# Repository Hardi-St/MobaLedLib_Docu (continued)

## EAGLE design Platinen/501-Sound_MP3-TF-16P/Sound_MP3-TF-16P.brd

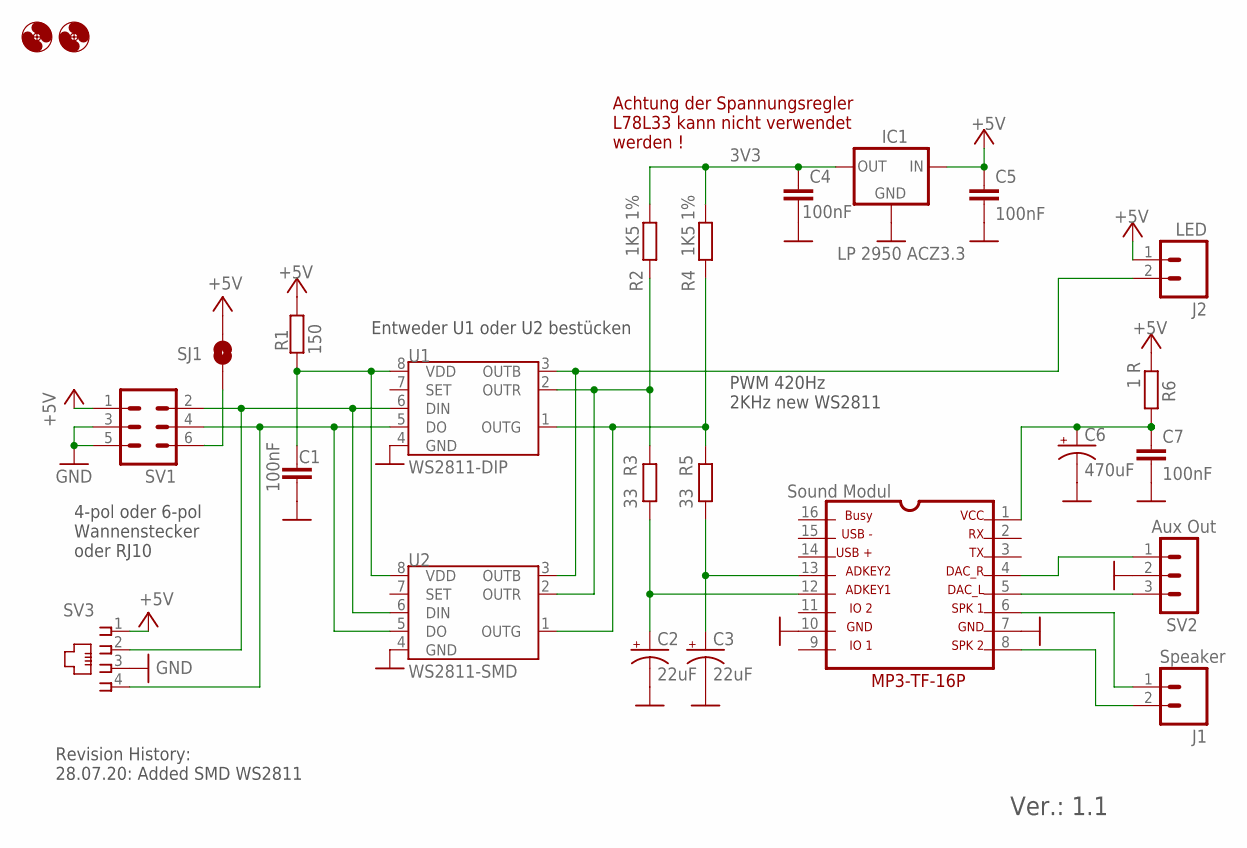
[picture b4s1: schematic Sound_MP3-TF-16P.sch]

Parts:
C1, C4, C5, C7: 100nF; CAP-PTH-SMALL-KIT
C2, C3: 22uF; CAPACITOR_CPOL-RADIAL-22UF
C6: 470uF; SPARKFUN-CAPACITORS_CPOL-RADIAL-100UF-25V
H1, H3: MOUNT-HOLE3.0; 3,0
IC1: LP 2950 ACZ3.3; 78LXX
J1: Speaker; 1X02
J2: LED; 1X02
MOD1: Sound Modul; MP3-TF-16P_MP3-TF-16P
R1: 150; RCL_0204/5
R2, R4: 1K5 1%; RCL_0204/5
R3, R5: 33; RCL_0204/5
R6: 1 R; RCL_0204/5
SJ1: Pin6 = 5V; SJ_2S-NO
SV1: ML6
SV2: Aux Out; MA03-1
SV3: RJ10RJ10_WO_OVERLAP; RJ10_NO_OVERLAP_BORDER
U1: WS2811-DIP; S3PO_MODUL_WS2811_SOUND_MP3-TF-16P_WS2811_AND_ATTINY_WS2811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
U2: WS2811-SMD; S3PO_MODUL_WS2811_SOUND_MP3-TF-16P_WS2811_AND_ATTINY_WS2811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

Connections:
3V3: C4.1, IC1.OUT, R2.1, R4.1
+5V: C5.1, IC1.IN, J2.1, R1.2, R6.1, SJ1.1, SV1.1, SV3.1
+5V1: SJ1.2, SV1.6
G1: R4.2, R5.1, U1.1 (OUTG), U2.1 (OUTG)
GND: C1.2, C2.2 (-), C3.2 (-), C4.2, C5.2, C6.2 (-), C7.2, IC1.GND, MOD1.7, MOD1.10, SV1.3, SV1.5, SV2.2, SV3.3, U1.4 (GND), U2.4 (GND)
unnamed: MOD1.5, SV2.3
unnamed: MOD1.4, SV2.1
unnamed: SV1.2, SV3.2, U1.6 (DIN), U2.6 (DIN)
unnamed: SV1.4, SV3.4, U1.5 (DO), U2.5 (DO)
unnamed: J1.1, MOD1.6
unnamed: J1.2, MOD1.8
unnamed: C2.1 (+), MOD1.12, R3.2
unnamed: C3.1 (+), MOD1.13, R5.2
unnamed: C6.1 (+), C7.1, MOD1.1, R6.2
unnamed: J2.2, U1.3 (OUTB), U2.3 (OUTB)
PWR1: C1.1, R1.1, U1.8 (VDD), U2.8 (VDD)
R1: R2.2, R3.1, U1.2 (OUTR), U2.2 (OUTR)

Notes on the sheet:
PWM 420Hz 2KHz new WS2811
4-pol oder 6-pol Wannenstecker oder RJ10
Achtung der Spannungsregler L78L33 kann nicht verwendet werden !
Revision History: 28.07.20: Added SMD WS2811
Ver.: 1.1
Entweder U1 oder U2 bestücken

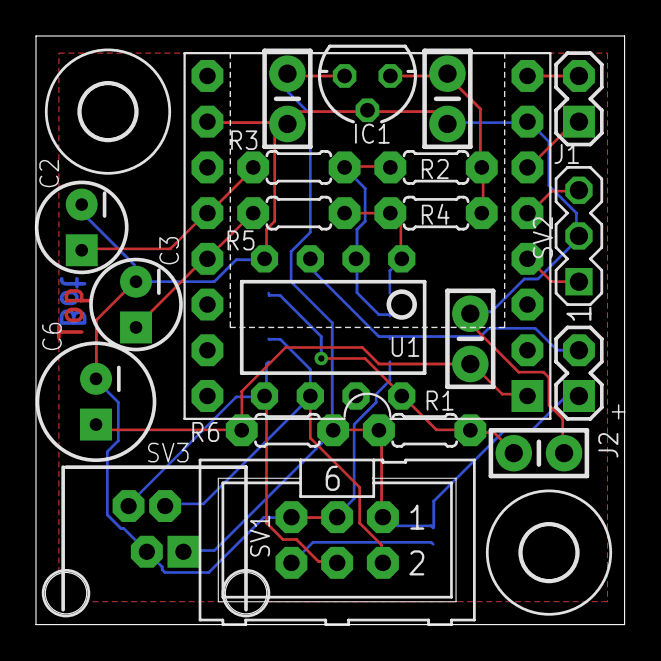
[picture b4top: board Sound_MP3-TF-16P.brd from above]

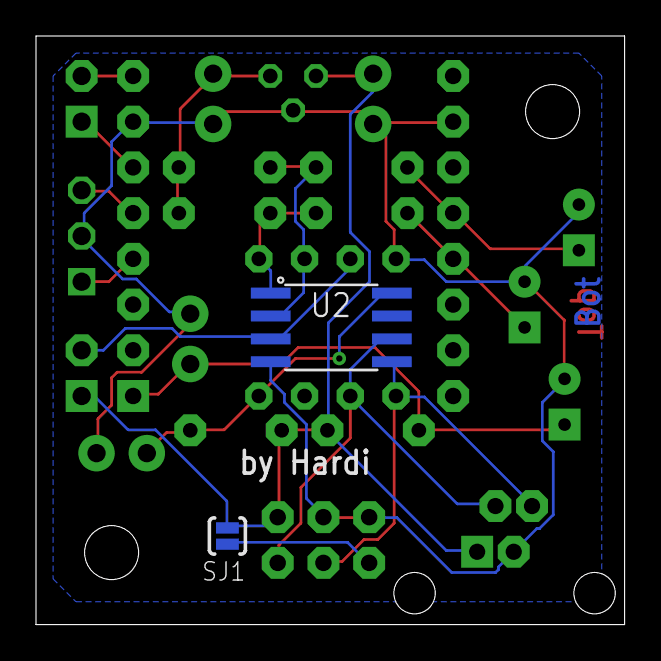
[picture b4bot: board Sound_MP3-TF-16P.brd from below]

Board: 2 copper layers, 32.7 x 32.7 mm, 25 parts (2 on the bottom side), 17 nets.

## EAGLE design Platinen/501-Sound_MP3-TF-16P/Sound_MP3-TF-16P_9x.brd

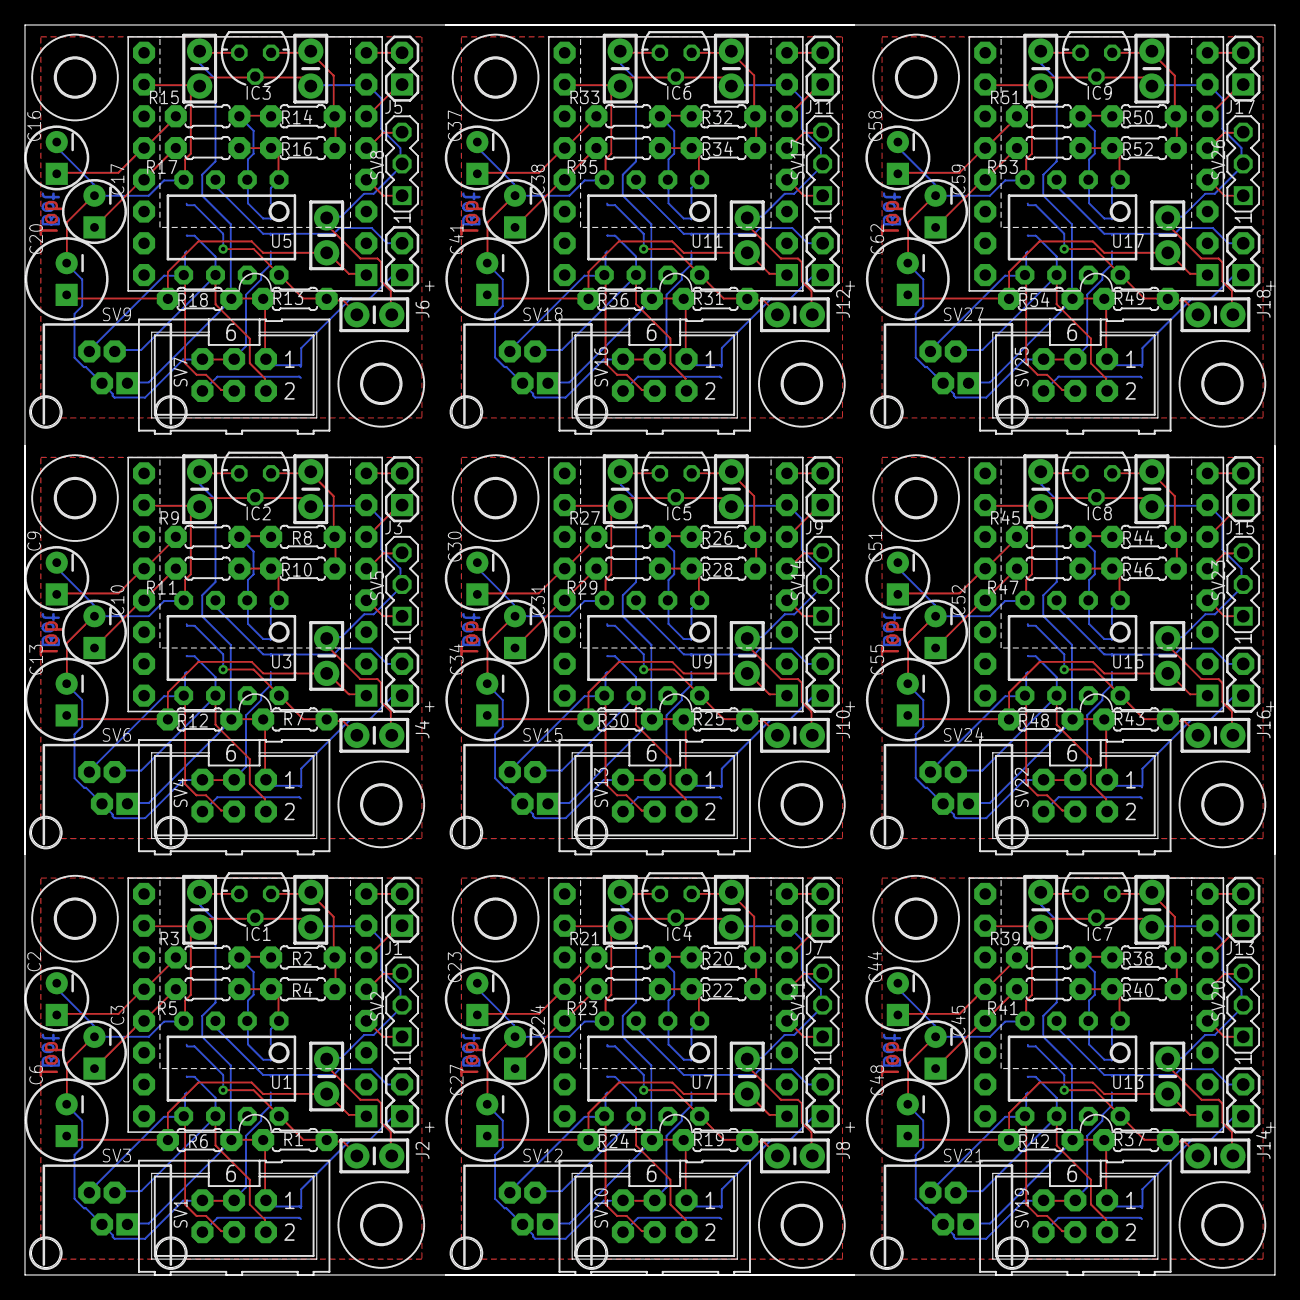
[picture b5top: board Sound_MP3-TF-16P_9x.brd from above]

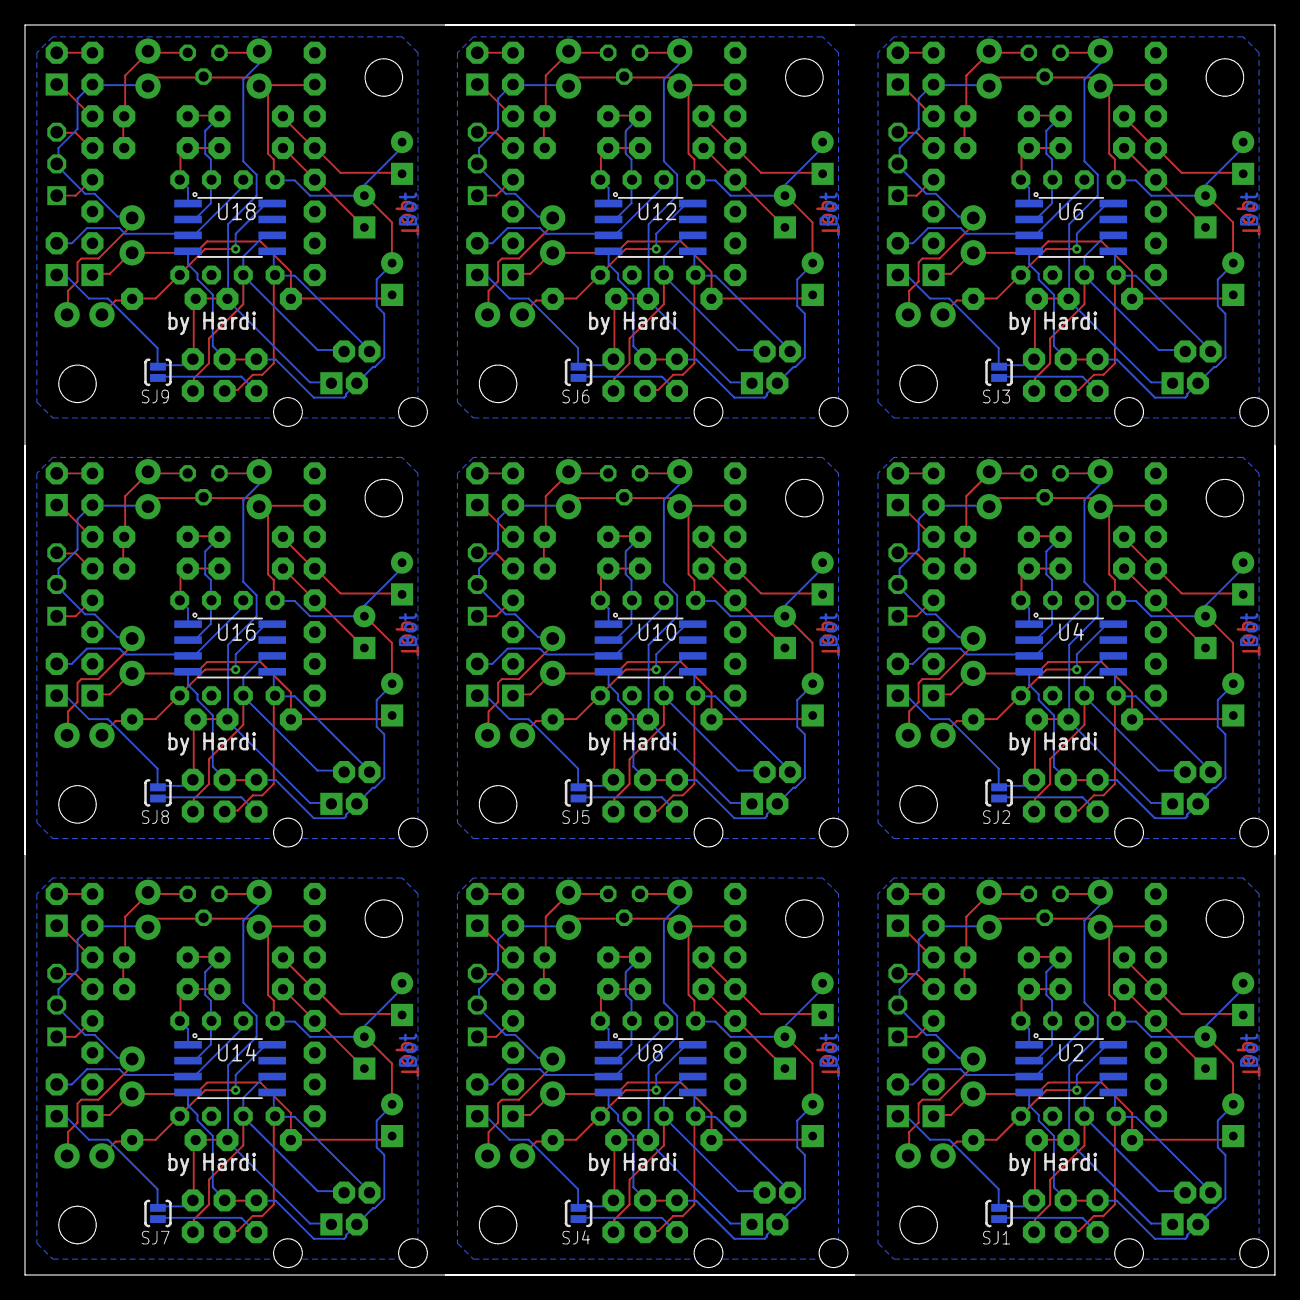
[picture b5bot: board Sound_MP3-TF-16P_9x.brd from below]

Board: 2 copper layers, 100.0 x 100.0 mm, 225 parts (18 on the bottom side), 153 nets.

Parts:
C1, C4, C5, C7, C8, C11, C12, C14, C15, C18, C19, C21, C22, C25, C26, C28, C29, C32, C33, C35, C36, C39, C40, C42, C43, C46, C47, C49, C50, C53, C54, C56, C57, C60, C61, C63: 100nF; CAP-PTH-SMALL-KIT
C2, C3, C9, C10, C16, C17, C23, C24, C30, C31, C37, C38, C44, C45, C51, C52, C58, C59: 22uF; CAPACITOR_CPOL-RADIAL-22UF
C6, C13, C20, C27, C34, C41, C48, C55, C62: 470uF; SPARKFUN-CAPACITORS_CPOL-RADIAL-100UF-25V
H1, H2, H3, H4, H5, H6, H7, H8, H9, H10, H11, H12, H13, H14, H15, H16, H17, H18: MOUNT-HOLE3.0; 3,0
IC1, IC2, IC3, IC4, IC5, IC6, IC7, IC8, IC9: LP 2950 ACZ3.3; 78LXX
J1, J3, J5, J7, J9, J11, J13, J15, J17: Speaker; 1X02
J2, J4, J6, J8, J10, J12, J14, J16, J18: LED; 1X02
MOD1, MOD2, MOD3, MOD4, MOD5, MOD6, MOD7, MOD8, MOD9: Sound Modul; MP3-TF-16P_MP3-TF-16P
R1, R7, R13, R19, R25, R31, R37, R43, R49: 150; RCL_0204/5
R2, R4, R8, R10, R14, R16, R20, R22, R26, R28, R32, R34, R38, R40, R44, R46, R50, R52: 1K5 1%; RCL_0204/5
R3, R5, R9, R11, R15, R17, R21, R23, R27, R29, R33, R35, R39, R41, R45, R47, R51, R53: 33; RCL_0204/5
R6, R12, R18, R24, R30, R36, R42, R48, R54: 1 R; RCL_0204/5
SJ1, SJ2, SJ3, SJ4, SJ5, SJ6, SJ7, SJ8, SJ9: Pin6 = 5V; SJ_2S-NO
SV1, SV4, SV7, SV10, SV13, SV16, SV19, SV22, SV25: ML6
SV2, SV5, SV8, SV11, SV14, SV17, SV20, SV23, SV26: Aux Out; MA03-1
SV3, SV6, SV9, SV12, SV15, SV18, SV21, SV24, SV27: RJ10RJ10_WO_OVERLAP; RJ10_NO_OVERLAP_BORDER
U1, U3, U5, U7, U9, U11, U13, U15, U17: WS2811-DIP; S3PO_MODUL_WS2811_SOUND_MP3-TF-16P_WS2811_AND_ATTINY_WS2811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
U2, U4, U6, U8, U10, U12, U14, U16, U18: WS2811-SMD; S3PO_MODUL_WS2811_SOUND_MP3-TF-16P_WS2811_AND_ATTINY_WS2811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

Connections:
3V1: C11.1, IC2.OUT, R8.1, R10.1
3V2: C18.1, IC3.OUT, R14.1, R16.1
3V3: C4.1, IC1.OUT, R2.1, R4.1
3V4: C25.1, IC4.OUT, R20.1, R22.1
3V5: C32.1, IC5.OUT, R26.1, R28.1
3V6: C39.1, IC6.OUT, R32.1, R34.1
3V7: C46.1, IC7.OUT, R38.1, R40.1
3V8: C53.1, IC8.OUT, R44.1, R46.1
3V9: C60.1, IC9.OUT, R50.1, R52.1
+5V: C5.1, IC1.IN, J2.1, R1.2, R6.1, SJ1.1, SV1.1, SV3.1
+5V1: SJ1.2, SV1.6
+5V2: C12.1, IC2.IN, J4.1, R7.2, R12.1, SJ2.1, SV4.1, SV6.1
+5V3: SJ2.2, SV4.6
+5V4: C19.1, IC3.IN, J6.1, R13.2, R18.1, SJ3.1, SV7.1, SV9.1
+5V5: SJ3.2, SV7.6
+5V6: C26.1, IC4.IN, J8.1, R19.2, R24.1, SJ4.1, SV10.1, SV12.1
+5V7: SJ4.2, SV10.6
+5V8: C33.1, IC5.IN, J10.1, R25.2, R30.1, SJ5.1, SV13.1, SV15.1
+5V9: SJ5.2, SV13.6
+5V10: C40.1, IC6.IN, J12.1, R31.2, R36.1, SJ6.1, SV16.1, SV18.1
+5V11: SJ6.2, SV16.6
+5V12: C47.1, IC7.IN, J14.1, R37.2, R42.1, SJ7.1, SV19.1, SV21.1
+5V13: SJ7.2, SV19.6
+5V14: C54.1, IC8.IN, J16.1, R43.2, R48.1, SJ8.1, SV22.1, SV24.1
+5V15: SJ8.2, SV22.6
+5V16: C61.1, IC9.IN, J18.1, R49.2, R54.1, SJ9.1, SV25.1, SV27.1
+5V17: SJ9.2, SV25.6
G1: R4.2, R5.1, U1.1, U2.1
G2: R10.2, R11.1, U3.1, U4.1
G3: R16.2, R17.1, U5.1, U6.1
G4: R22.2, R23.1, U7.1, U8.1
G5: R28.2, R29.1, U9.1, U10.1
G6: R34.2, R35.1, U11.1, U12.1
G7: R40.2, R41.1, U13.1, U14.1
G8: R46.2, R47.1, U15.1, U16.1
G9: R52.2, R53.1, U17.1, U18.1
GND: C1.2, C2.2, C3.2, C4.2, C5.2, C6.2, C7.2, IC1.GND, MOD1.7, MOD1.10, SV1.3, SV1.5, SV2.2, SV3.3, U1.4, U2.4
GND1: C8.2, C9.2, C10.2, C11.2, C12.2, C13.2, C14.2, IC2.GND, MOD2.7, MOD2.10, SV4.3, SV4.5, SV5.2, SV6.3, U3.4, U4.4
GND2: C15.2, C16.2, C17.2, C18.2, C19.2, C20.2, C21.2, IC3.GND, MOD3.7, MOD3.10, SV7.3, SV7.5, SV8.2, SV9.3, U5.4, U6.4
GND3: C22.2, C23.2, C24.2, C25.2, C26.2, C27.2, C28.2, IC4.GND, MOD4.7, MOD4.10, SV10.3, SV10.5, SV11.2, SV12.3, U7.4, U8.4
GND4: C29.2, C30.2, C31.2, C32.2, C33.2, C34.2, C35.2, IC5.GND, MOD5.7, MOD5.10, SV13.3, SV13.5, SV14.2, SV15.3, U9.4, U10.4
GND5: C36.2, C37.2, C38.2, C39.2, C40.2, C41.2, C42.2, IC6.GND, MOD6.7, MOD6.10, SV16.3, SV16.5, SV17.2, SV18.3, U11.4, U12.4
GND6: C43.2, C44.2, C45.2, C46.2, C47.2, C48.2, C49.2, IC7.GND, MOD7.7, MOD7.10, SV19.3, SV19.5, SV20.2, SV21.3, U13.4, U14.4
GND7: C50.2, C51.2, C52.2, C53.2, C54.2, C55.2, C56.2, IC8.GND, MOD8.7, MOD8.10, SV22.3, SV22.5, SV23.2, SV24.3, U15.4, U16.4
GND8: C57.2, C58.2, C59.2, C60.2, C61.2, C62.2, C63.2, IC9.GND, MOD9.7, MOD9.10, SV25.3, SV25.5, SV26.2, SV27.3, U17.4, U18.4
unnamed: MOD1.5, SV2.3
unnamed: MOD1.4, SV2.1
unnamed: SV1.2, SV3.2, U1.6, U2.6
unnamed: SV1.4, SV3.4, U1.5, U2.5
unnamed: J1.1, MOD1.6
unnamed: J1.2, MOD1.8
unnamed: C2.1, MOD1.12, R3.2
unnamed: C3.1, MOD1.13, R5.2
unnamed: C6.1, C7.1, MOD1.1, R6.2
unnamed: J2.2, U1.3, U2.3
unnamed: C13.1, C14.1, MOD2.1, R12.2
unnamed: C9.1, MOD2.12, R9.2
unnamed: C10.1, MOD2.13, R11.2
unnamed: SV4.2, SV6.2, U3.6, U4.6
unnamed: SV4.4, SV6.4, U3.5, U4.5
unnamed: MOD2.5, SV5.3
unnamed: MOD2.4, SV5.1
unnamed: J3.1, MOD2.6
unnamed: J3.2, MOD2.8
unnamed: J4.2, U3.3, U4.3
unnamed: C20.1, C21.1, MOD3.1, R18.2
unnamed: C16.1, MOD3.12, R15.2
unnamed: C17.1, MOD3.13, R17.2
unnamed: SV7.2, SV9.2, U5.6, U6.6
unnamed: SV7.4, SV9.4, U5.5, U6.5
unnamed: MOD3.5, SV8.3
unnamed: MOD3.4, SV8.1
unnamed: J5.1, MOD3.6
unnamed: J5.2, MOD3.8
unnamed: J6.2, U5.3, U6.3
unnamed: C27.1, C28.1, MOD4.1, R24.2
unnamed: C23.1, MOD4.12, R21.2
unnamed: C24.1, MOD4.13, R23.2
unnamed: SV10.2, SV12.2, U7.6, U8.6
unnamed: SV10.4, SV12.4, U7.5, U8.5
unnamed: MOD4.5, SV11.3
unnamed: MOD4.4, SV11.1
unnamed: J7.1, MOD4.6
unnamed: J7.2, MOD4.8
unnamed: J8.2, U7.3, U8.3
unnamed: C34.1, C35.1, MOD5.1, R30.2
unnamed: C30.1, MOD5.12, R27.2
unnamed: C31.1, MOD5.13, R29.2
unnamed: SV13.2, SV15.2, U9.6, U10.6
unnamed: SV13.4, SV15.4, U9.5, U10.5
unnamed: MOD5.5, SV14.3
unnamed: MOD5.4, SV14.1
unnamed: J9.1, MOD5.6
unnamed: J9.2, MOD5.8
unnamed: J10.2, U9.3, U10.3
unnamed: C41.1, C42.1, MOD6.1, R36.2
unnamed: C37.1, MOD6.12, R33.2
unnamed: C38.1, MOD6.13, R35.2
unnamed: SV16.2, SV18.2, U11.6, U12.6
unnamed: SV16.4, SV18.4, U11.5, U12.5
unnamed: MOD6.5, SV17.3
unnamed: MOD6.4, SV17.1
unnamed: J11.1, MOD6.6
unnamed: J11.2, MOD6.8
unnamed: J12.2, U11.3, U12.3
unnamed: C48.1, C49.1, MOD7.1, R42.2
unnamed: C44.1, MOD7.12, R39.2
unnamed: C45.1, MOD7.13, R41.2
unnamed: SV19.2, SV21.2, U13.6, U14.6
unnamed: SV19.4, SV21.4, U13.5, U14.5
unnamed: MOD7.5, SV20.3
unnamed: MOD7.4, SV20.1
unnamed: J13.1, MOD7.6
unnamed: J13.2, MOD7.8
unnamed: J14.2, U13.3, U14.3
unnamed: C55.1, C56.1, MOD8.1, R48.2
unnamed: C51.1, MOD8.12, R45.2
unnamed: C52.1, MOD8.13, R47.2
unnamed: SV22.2, SV24.2, U15.6, U16.6
unnamed: SV22.4, SV24.4, U15.5, U16.5
unnamed: MOD8.5, SV23.3
unnamed: MOD8.4, SV23.1
unnamed: J15.1, MOD8.6
unnamed: J15.2, MOD8.8
unnamed: J16.2, U15.3, U16.3
unnamed: C62.1, C63.1, MOD9.1, R54.2
unnamed: C58.1, MOD9.12, R51.2
unnamed: C59.1, MOD9.13, R53.2
unnamed: SV25.2, SV27.2, U17.6, U18.6
unnamed: SV25.4, SV27.4, U17.5, U18.5
unnamed: MOD9.5, SV26.3
unnamed: MOD9.4, SV26.1
unnamed: J17.1, MOD9.6
unnamed: J17.2, MOD9.8
unnamed: J18.2, U17.3, U18.3
PWR1: C1.1, R1.1, U1.8, U2.8
PWR2: C8.1, R7.1, U3.8, U4.8
PWR3: C15.1, R13.1, U5.8, U6.8
PWR4: C22.1, R19.1, U7.8, U8.8
PWR5: C29.1, R25.1, U9.8, U10.8
PWR6: C36.1, R31.1, U11.8, U12.8
PWR7: C43.1, R37.1, U13.8, U14.8
PWR8: C50.1, R43.1, U15.8, U16.8
PWR9: C57.1, R49.1, U17.8, U18.8
R1: R2.2, R3.1, U1.2, U2.2
R2: R8.2, R9.1, U3.2, U4.2
R3: R14.2, R15.1, U5.2, U6.2
R4: R20.2, R21.1, U7.2, U8.2
R5: R26.2, R27.1, U9.2, U10.2
R6: R32.2, R33.1, U11.2, U12.2
R7: R38.2, R39.1, U13.2, U14.2
R8: R44.2, R45.1, U15.2, U16.2
R9: R50.2, R51.1, U17.2, U18.2

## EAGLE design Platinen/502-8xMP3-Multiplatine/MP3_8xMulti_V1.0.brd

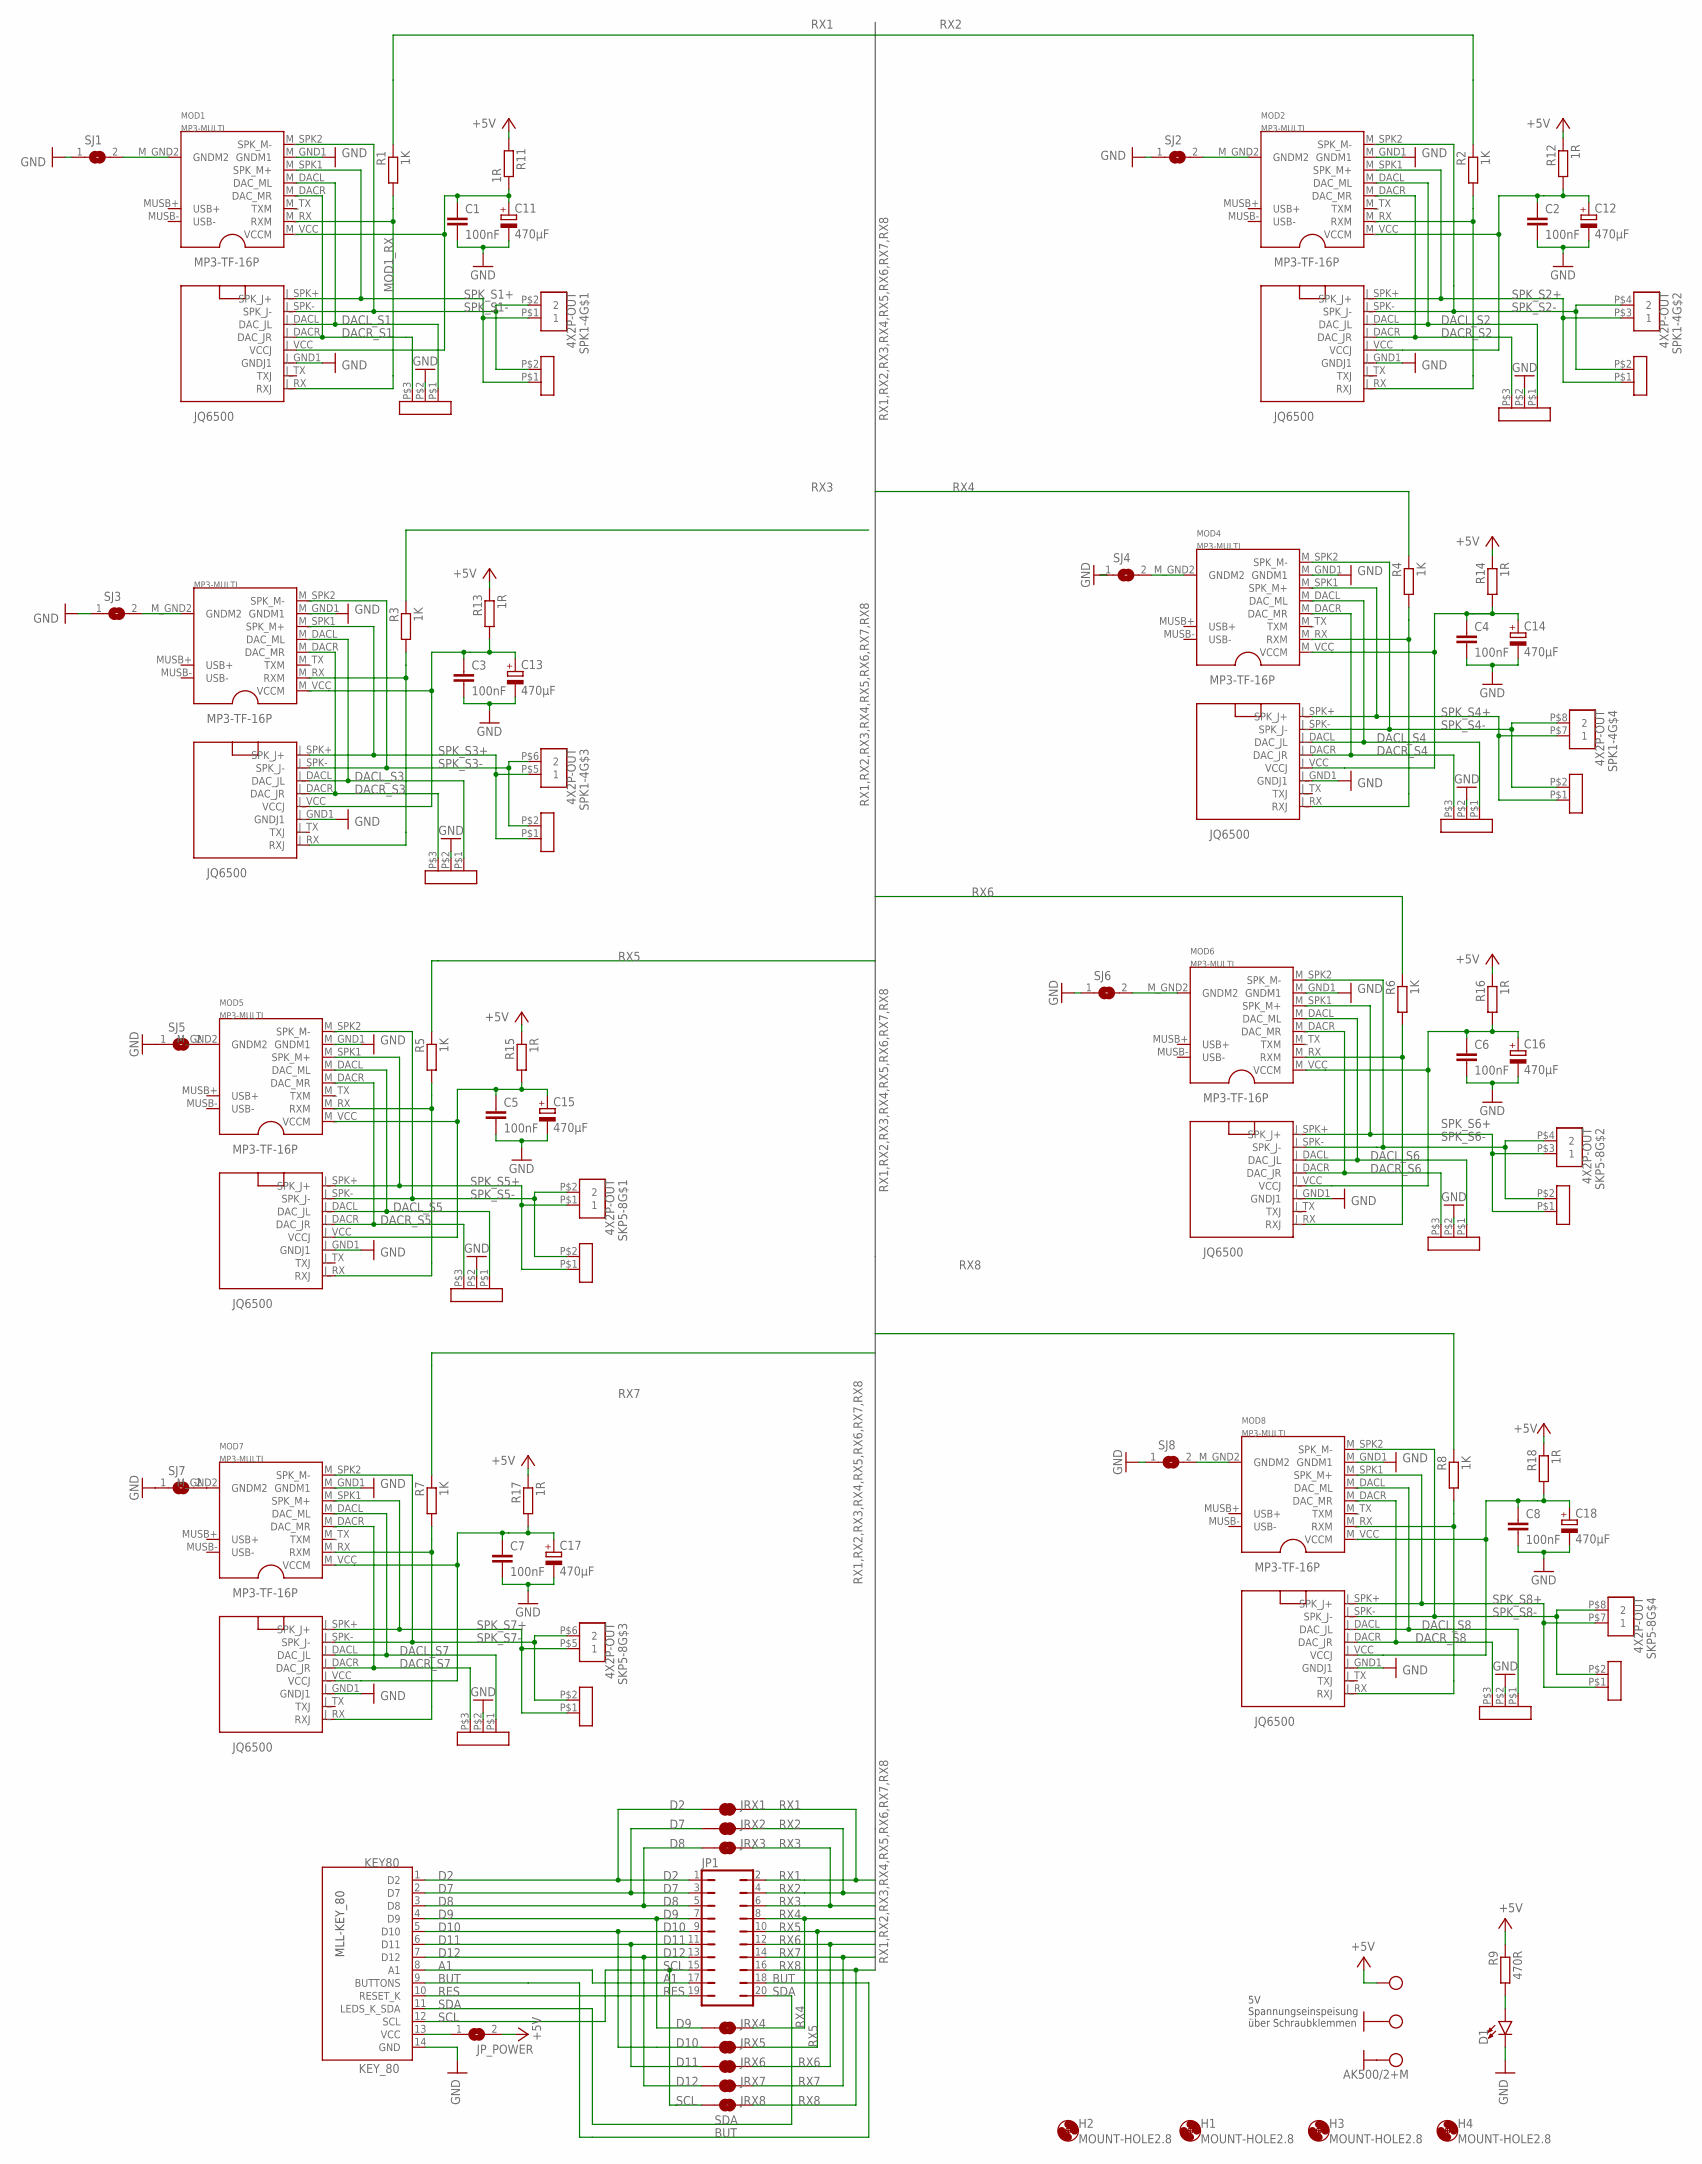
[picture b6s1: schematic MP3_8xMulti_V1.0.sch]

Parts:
C1, C2, C3, C4, C5, C6, C7, C8: 100nF; C025-025X050
C11, C12, C13, C14, C15, C16, C17, C18: 470µF; E5-8,5
D1: LED3MM; LED_3MM
DAC1, DAC2, DAC3, DAC4, DAC5, DAC6, DAC7, DAC8: 3XRM254
H1, H2, H3, H4: MOUNT-HOLE2.8; 2,8
JP1: JP10Q
JP_POWER: SJ
JRX1, JRX2, JRX3, JRX4, JRX5, JRX6, JRX7, JRX8: JUMPER-SMT_2_NC_TRACE_NO-SILK; SMT-JUMPER_2_NC_TRACE_NO-SILK
KEY80: KEY_80; IDC14
MOD1, MOD2, MOD3, MOD4, MOD5, MOD6, MOD7, MOD8: MP3-MULTI; MP3-TF16P_JQ6500
R1, R2, R3, R4, R5, R6, R7, R8: 1K; 0207/7
R9: 470R; 0207/7
R11, R12, R13, R14, R15, R16, R17, R18: 1R; 0207/7
SJ1, SJ2, SJ3, SJ4, SJ5, SJ6, SJ7, SJ8: SJ
SKP5-8: 4X2P-OUT; DG308
SPK1, SPK2, SPK3, SPK4, SPK5, SPK6, SPK7, SPK8: 2XRM254
SPK1-4: 4X2P-OUT; DG308
X1: AK500/2+M

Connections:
+5V: JP_POWER.2, R9.1, R11.2, R12.1, R13.1, R14.1, R15.1, R16.1, R17.1, R18.1, X1.2
A1: JP1.17, KEY80.8 (A1)
BUT: JP1.18, KEY80.9 (BUTTONS)
D2: JP1.1, JRX1.1, KEY80.1 (D2)
D7: JP1.3, JRX2.1, KEY80.2 (D7)
D8: JP1.5, JRX3.1, KEY80.3 (D8)
D9: JP1.7, JRX4.1, KEY80.4 (D9)
D10: JP1.9, JRX5.1, KEY80.5 (D10)
D11: JP1.11, JRX6.1, KEY80.6 (D11)
D12: JP1.13, JRX7.1, KEY80.7 (D12)
DACL_S1: DAC1.P$1, MOD1.J_DACL (DAC_JL), MOD1.M_DACL (DAC_ML)
DACL_S2: DAC2.P$1, MOD2.J_DACL (DAC_JL), MOD2.M_DACL (DAC_ML)
DACL_S3: DAC3.P$1, MOD3.J_DACL (DAC_JL), MOD3.M_DACL (DAC_ML)
DACL_S4: DAC4.P$1, MOD4.J_DACL (DAC_JL), MOD4.M_DACL (DAC_ML)
DACL_S5: DAC5.P$1, MOD5.J_DACL (DAC_JL), MOD5.M_DACL (DAC_ML)
DACL_S6: DAC6.P$1, MOD6.J_DACL (DAC_JL), MOD6.M_DACL (DAC_ML)
DACL_S7: DAC7.P$1, MOD7.J_DACL (DAC_JL), MOD7.M_DACL (DAC_ML)
DACL_S8: DAC8.P$1, MOD8.J_DACL (DAC_JL), MOD8.M_DACL (DAC_ML)
DACR_S1: DAC1.P$3, MOD1.J_DACR (DAC_JR), MOD1.M_DACR (DAC_MR)
DACR_S2: DAC2.P$3, MOD2.J_DACR (DAC_JR), MOD2.M_DACR (DAC_MR)
DACR_S3: DAC3.P$3, MOD3.J_DACR (DAC_JR), MOD3.M_DACR (DAC_MR)
DACR_S4: DAC4.P$3, MOD4.J_DACR (DAC_JR), MOD4.M_DACR (DAC_MR)
DACR_S5: DAC5.P$3, MOD5.J_DACR (DAC_JR), MOD5.M_DACR (DAC_MR)
DACR_S6: DAC6.P$3, MOD6.J_DACR (DAC_JR), MOD6.M_DACR (DAC_MR)
DACR_S7: DAC7.P$3, MOD7.J_DACR (DAC_JR), MOD7.M_DACR (DAC_MR)
DACR_S8: DAC8.P$3, MOD8.J_DACR (DAC_JR), MOD8.M_DACR (DAC_MR)
GND: C1.2, C2.2, C3.2, C4.2, C5.2, C6.2, C7.2, C8.2, C11.-, C12.-, C13.-, C14.-, C15.-, C16.-, C17.-, C18.-, D1.K (C), DAC1.P$2, DAC2.P$2, DAC3.P$2, DAC4.P$2, DAC5.P$2, DAC6.P$2, DAC7.P$2, DAC8.P$2, KEY80.14 (GND), MOD1.J_GND1 (GNDJ1), MOD1.M_GND1 (GNDM1), MOD2.J_GND1 (GNDJ1), MOD2.M_GND1 (GNDM1), MOD3.J_GND1 (GNDJ1), MOD3.M_GND1 (GNDM1), MOD4.J_GND1 (GNDJ1), MOD4.M_GND1 (GNDM1), MOD5.J_GND1 (GNDJ1), MOD5.M_GND1 (GNDM1), MOD6.J_GND1 (GNDJ1), MOD6.M_GND1 (GNDM1), MOD7.J_GND1 (GNDJ1), MOD7.M_GND1 (GNDM1), MOD8.J_GND1 (GNDJ1), MOD8.M_GND1 (GNDM1), SJ1.1, SJ2.1, SJ3.1, SJ4.1, SJ5.1, SJ6.1, SJ7.1, SJ8.1, X1.1, X1.M
LED1: D1.A, R9.2
MOD1_RX: MOD1.J_RX (RXJ), MOD1.M_RX (RXM), R1.2
MOD1_RX1: MOD2.J_RX (RXJ), MOD2.M_RX (RXM), R2.2
MOD1_RX2: MOD3.J_RX (RXJ), MOD3.M_RX (RXM), R3.2
MOD1_RX3: MOD4.J_RX (RXJ), MOD4.M_RX (RXM), R4.2
MOD1_RX4: MOD5.J_RX (RXJ), MOD5.M_RX (RXM), R5.2
MOD1_RX5: MOD6.J_RX (RXJ), MOD6.M_RX (RXM), R6.2
MOD1_RX6: MOD7.J_RX (RXJ), MOD7.M_RX (RXM), R7.2
MOD1_RX7: MOD8.J_RX (RXJ), MOD8.M_RX (RXM), R8.2
M_GND1: MOD1.M_GND2 (GNDM2), SJ1.2
M_GND2: MOD2.M_GND2 (GNDM2), SJ2.2
M_GND3: MOD3.M_GND2 (GNDM2), SJ3.2
M_GND4: MOD4.M_GND2 (GNDM2), SJ4.2
M_GND5: MOD5.M_GND2 (GNDM2), SJ5.2
M_GND6: MOD6.M_GND2 (GNDM2), SJ6.2
M_GND7: MOD7.M_GND2 (GNDM2), SJ7.2
M_GND8: MOD8.M_GND2 (GNDM2), SJ8.2
OPT-VCC: JP_POWER.1, KEY80.13 (VCC)
RES: JP1.19, KEY80.10 (RESET_K)
RX1: JP1.2, JRX1.2, R1.1
RX2: JP1.4, JRX2.2, R2.1
RX3: JP1.6, JRX3.2, R3.1
RX4: JP1.8, JRX4.2, R4.1
RX5: JP1.10, JRX5.2, R5.1
RX6: JP1.12, JRX6.2, R6.1
RX7: JP1.14, JRX7.2, R7.1
RX8: JP1.16, JRX8.2, R8.1
SCL: JP1.15, JRX8.1, KEY80.12 (SCL)
SDA: JP1.20, KEY80.11 (LEDS_K_SDA)
SOUND1_VCC: C1.1, C11.+, MOD1.J_VCC (VCCJ), MOD1.M_VCC (VCCM), R11.1
SOUND2_VCC: C2.1, C12.+, MOD2.J_VCC (VCCJ), MOD2.M_VCC (VCCM), R12.2
SOUND3_VCC: C3.1, C13.+, MOD3.J_VCC (VCCJ), MOD3.M_VCC (VCCM), R13.2
SOUND4_VCC: C4.1, C14.+, MOD4.J_VCC (VCCJ), MOD4.M_VCC (VCCM), R14.2
SOUND5_VCC: C5.1, C15.+, MOD5.J_VCC (VCCJ), MOD5.M_VCC (VCCM), R15.2
SOUND6_VCC: C6.1, C16.+, MOD6.J_VCC (VCCJ), MOD6.M_VCC (VCCM), R16.2
SOUND7_VCC: C7.1, C17.+, MOD7.J_VCC (VCCJ), MOD7.M_VCC (VCCM), R17.2
SOUND8_VCC: C8.1, C18.+, MOD8.J_VCC (VCCJ), MOD8.M_VCC (VCCM), R18.2
SPK_S1+: MOD1.J_SPK+ (SPK_J+), MOD1.M_SPK1 (SPK_M+), SPK1.P$1, SPK1-4.P$1 (1)
SPK_S1-: MOD1.J_SPK- (SPK_J-), MOD1.M_SPK2 (SPK_M-), SPK1.P$2, SPK1-4.P$2 (2)
SPK_S2+: MOD2.J_SPK+ (SPK_J+), MOD2.M_SPK1 (SPK_M+), SPK1-4.P$3 (1), SPK2.P$1
SPK_S2-: MOD2.J_SPK- (SPK_J-), MOD2.M_SPK2 (SPK_M-), SPK1-4.P$4 (2), SPK2.P$2
SPK_S3+: MOD3.J_SPK+ (SPK_J+), MOD3.M_SPK1 (SPK_M+), SPK1-4.P$5 (1), SPK3.P$1
SPK_S3-: MOD3.J_SPK- (SPK_J-), MOD3.M_SPK2 (SPK_M-), SPK1-4.P$6 (2), SPK3.P$2
SPK_S4+: MOD4.J_SPK+ (SPK_J+), MOD4.M_SPK1 (SPK_M+), SPK1-4.P$7 (1), SPK4.P$1
SPK_S4-: MOD4.J_SPK- (SPK_J-), MOD4.M_SPK2 (SPK_M-), SPK1-4.P$8 (2), SPK4.P$2
SPK_S5+: MOD5.J_SPK+ (SPK_J+), MOD5.M_SPK1 (SPK_M+), SKP5-8.P$1 (1), SPK5.P$1
SPK_S5-: MOD5.J_SPK- (SPK_J-), MOD5.M_SPK2 (SPK_M-), SKP5-8.P$2 (2), SPK5.P$2
SPK_S6+: MOD6.J_SPK+ (SPK_J+), MOD6.M_SPK1 (SPK_M+), SKP5-8.P$3 (1), SPK6.P$1
SPK_S6-: MOD6.J_SPK- (SPK_J-), MOD6.M_SPK2 (SPK_M-), SKP5-8.P$4 (2), SPK6.P$2
SPK_S7+: MOD7.J_SPK+ (SPK_J+), MOD7.M_SPK1 (SPK_M+), SKP5-8.P$5 (1), SPK7.P$1
SPK_S7-: MOD7.J_SPK- (SPK_J-), MOD7.M_SPK2 (SPK_M-), SKP5-8.P$6 (2), SPK7.P$2
SPK_S8+: MOD8.J_SPK+ (SPK_J+), MOD8.M_SPK1 (SPK_M+), SKP5-8.P$7 (1), SPK8.P$1
SPK_S8-: MOD8.J_SPK- (SPK_J-), MOD8.M_SPK2 (SPK_M-), SKP5-8.P$8 (2), SPK8.P$2

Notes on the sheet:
5V Spannungseinspeisung über Schraubklemmen

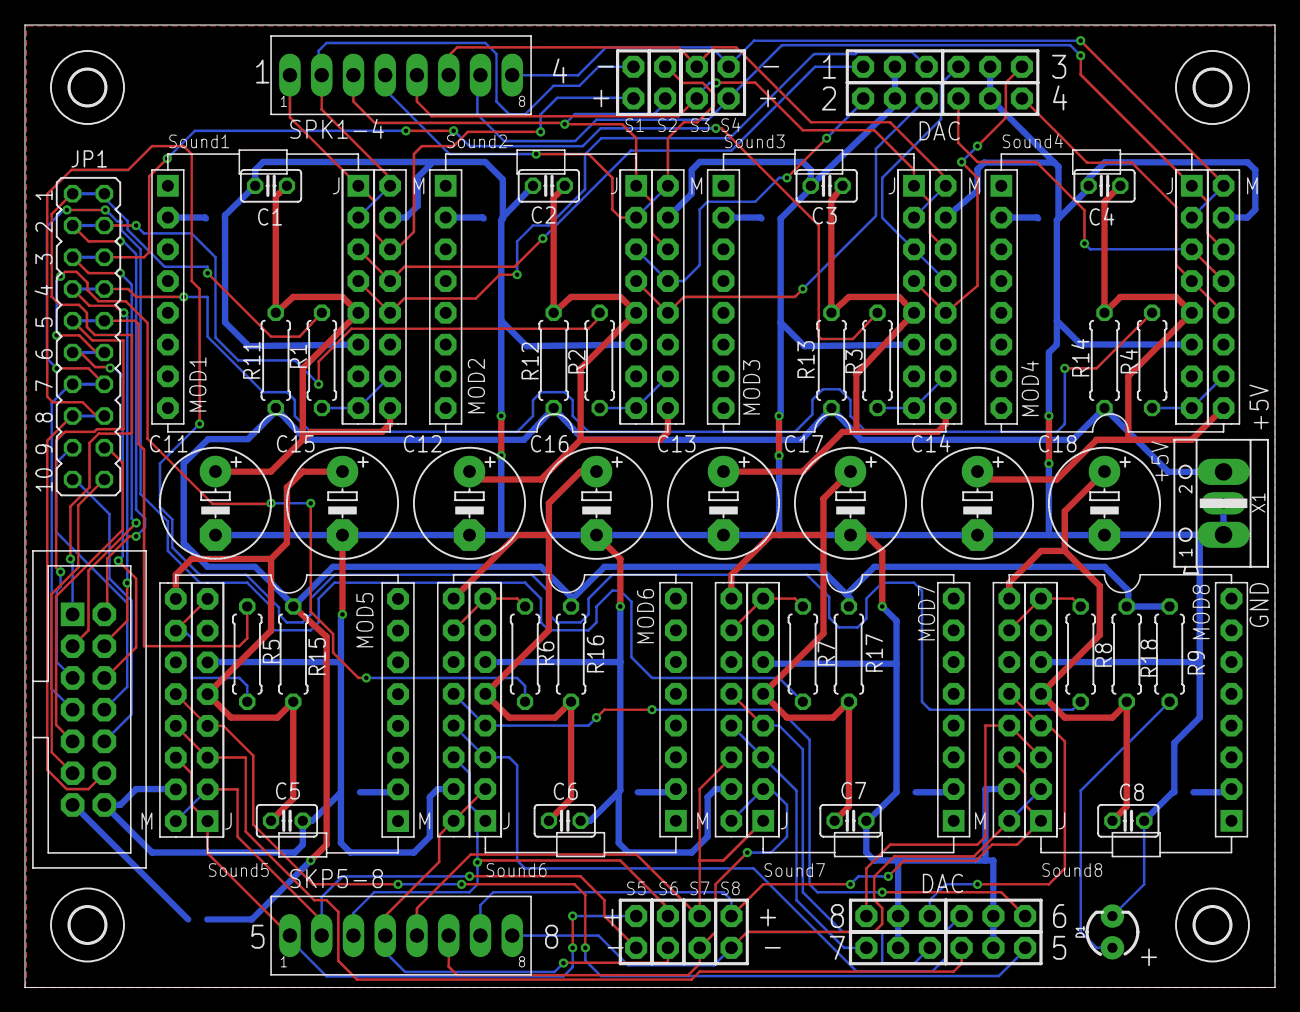
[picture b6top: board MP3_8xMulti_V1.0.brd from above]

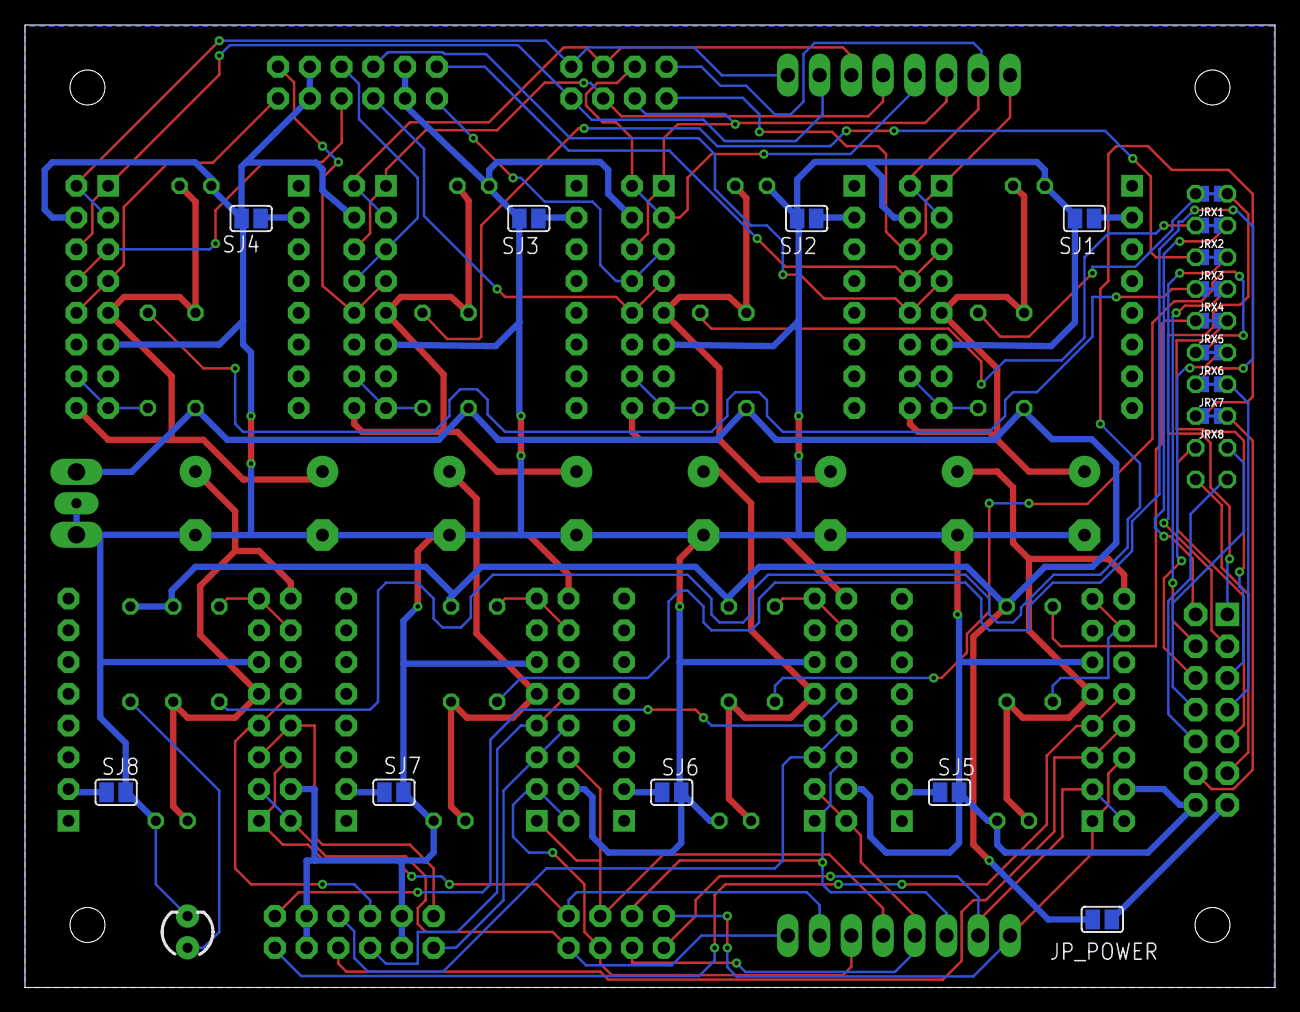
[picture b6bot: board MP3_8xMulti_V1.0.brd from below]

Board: 2 copper layers, 100.0 x 77.0 mm, 84 parts (17 on the bottom side), 80 nets.
